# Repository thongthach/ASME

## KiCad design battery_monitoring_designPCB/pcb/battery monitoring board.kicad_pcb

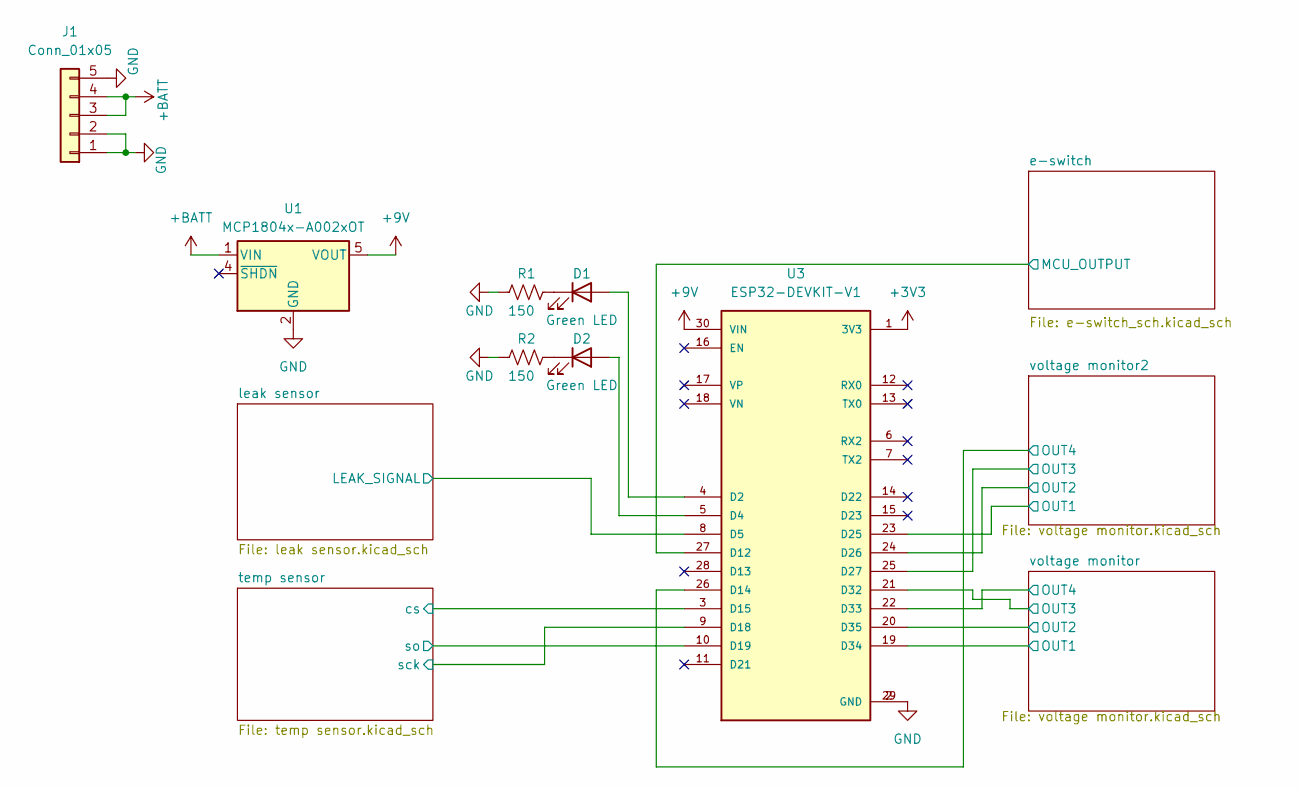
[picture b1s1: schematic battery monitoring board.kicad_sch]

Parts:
D1, D2: Green LED; D_0805_2012Metric_Pad1.15x1.40mm_HandSolder
J1: Conn_01x05; 1x5 Screw, 39970-0105 MOLEX
R1, R2: 150; R_0805_2012Metric_Pad1.20x1.40mm_HandSolder
U1: MCP1804x-A002xOT; SOT-23-5
U3: ESP32-DEVKIT-V1; MODULE_ESP32_DEVKIT_V1; PARTREV N/A

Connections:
+3V3: U3.1 (3V3); also elsewhere on the board
+9V: U1.5 (VOUT), U3.30 (VIN); also elsewhere on the board
+BATT: J1.3, J1.4, U1.1 (VIN); also elsewhere on the board
/e-switch/MCU_OUTPUT: U3.27 (D12); also elsewhere on the board
/leak sensor/LEAK_SIGNAL: U3.8 (D5); also elsewhere on the board
/temp sensor/cs: U3.3 (D15); also elsewhere on the board
/temp sensor/sck: U3.9 (D18); also elsewhere on the board
/temp sensor/so: U3.10 (D19); also elsewhere on the board
/voltage monitor2/OUT1: U3.23 (D25); also elsewhere on the board
/voltage monitor2/OUT2: U3.24 (D26); also elsewhere on the board
/voltage monitor2/OUT3: U3.25 (D27); also elsewhere on the board
/voltage monitor2/OUT4: U3.26 (D14); also elsewhere on the board
/voltage monitor/OUT1: U3.19 (D34); also elsewhere on the board
/voltage monitor/OUT2: U3.20 (D35); also elsewhere on the board
/voltage monitor/OUT3: U3.21 (D32); also elsewhere on the board
/voltage monitor/OUT4: U3.22 (D33); also elsewhere on the board
GND: J1.1, J1.2, J1.5, R1.1, R2.1, U1.2 (GND), U3.2 (GND), U3.29 (GND); also elsewhere on the board
unnamed: D1.2 (A), U3.4 (D2)
unnamed: D1.1 (K), R1.2
unnamed: D2.2 (A), U3.5 (D4)
unnamed: D2.1 (K), R2.2

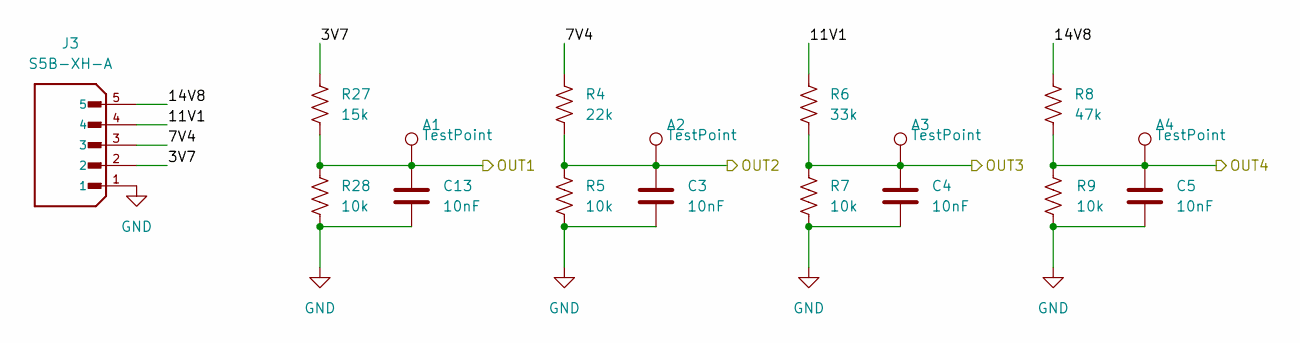
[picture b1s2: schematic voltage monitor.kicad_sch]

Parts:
A1, A2, A3, A4: TestPoint; TestPoint_Pad_1.0x1.0mm
C3, C4, C5, C13: 10nF; C_0805_2012Metric_Pad1.18x1.45mm_HandSolder
J3: S5B-XH-A; JST_S5B-XH-A; PARTREV 27-1-20
R4: 22k; R_0805_2012Metric_Pad1.20x1.40mm_HandSolder
R5, R7, R9, R28: 10k; R_0805_2012Metric_Pad1.20x1.40mm_HandSolder
R6: 33k; R_0805_2012Metric_Pad1.20x1.40mm_HandSolder
R8: 47k; R_0805_2012Metric_Pad1.20x1.40mm_HandSolder
R27: 15k; R_0805_2012Metric_Pad1.20x1.40mm_HandSolder

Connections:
/voltage monitor/3V7: J3.2, R27.2
/voltage monitor/7V4: J3.3, R4.2
/voltage monitor/11V1: J3.4, R6.2
/voltage monitor/14V8: J3.5, R8.2
/voltage monitor/OUT1: A1.1, C13.1, R27.1, R28.1; also elsewhere on the board
/voltage monitor/OUT2: A2.1, C3.1, R4.1, R5.1; also elsewhere on the board
/voltage monitor/OUT3: A3.1, C4.1, R6.1, R7.1; also elsewhere on the board
/voltage monitor/OUT4: A4.1, C5.1, R8.1, R9.2; also elsewhere on the board
GND: C3.2, C4.2, C5.2, C13.2, J3.1, R5.2, R7.2, R9.1, R28.2; also elsewhere on the board

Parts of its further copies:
B1, B2, B3, B4: TestPoint; TestPoint_Pad_1.0x1.0mm
C10, C11, C12, C14: 10nF; C_0805_2012Metric_Pad1.18x1.45mm_HandSolder
J9: S5B-XH-A; JST_S5B-XH-A; PARTREV 27-1-20
R20: 22k; R_0805_2012Metric_Pad1.20x1.40mm_HandSolder
R21, R23, R25, R30: 10k; R_0805_2012Metric_Pad1.20x1.40mm_HandSolder
R22: 33k; R_0805_2012Metric_Pad1.20x1.40mm_HandSolder
R24: 47k; R_0805_2012Metric_Pad1.20x1.40mm_HandSolder
R29: 15k; R_0805_2012Metric_Pad1.20x1.40mm_HandSolder

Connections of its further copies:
/voltage monitor2/3V7: J9.2, R29.2
/voltage monitor2/7V4: J9.3, R20.2
/voltage monitor2/11V1: J9.4, R22.2
/voltage monitor2/14V8: J9.5, R24.2
/voltage monitor2/OUT1: B1.1, C14.1, R29.1, R30.1; also elsewhere on the board
/voltage monitor2/OUT2: B2.1, C10.1, R20.1, R21.1; also elsewhere on the board
/voltage monitor2/OUT3: B3.1, C11.1, R22.1, R23.1; also elsewhere on the board
/voltage monitor2/OUT4: B4.1, C12.1, R24.1, R25.2; also elsewhere on the board
GND: C10.2, C11.2, C12.2, C14.2, J9.1, R21.2, R23.2, R25.1, R30.2; also elsewhere on the board

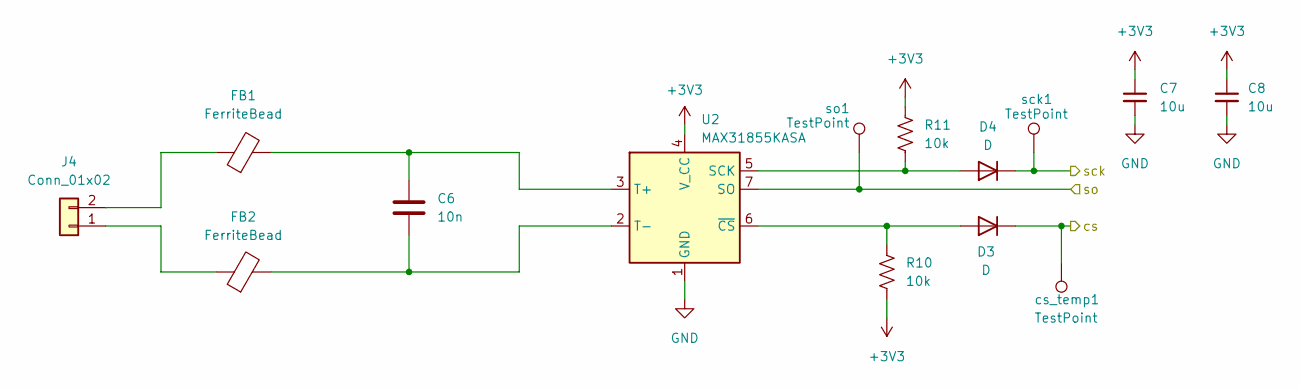
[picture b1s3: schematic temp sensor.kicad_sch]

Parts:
C6: 10n; C_0805_2012Metric_Pad1.18x1.45mm_HandSolder
C7, C8: 10u; C_0805_2012Metric_Pad1.18x1.45mm_HandSolder
D3, D4: D; D_0805_2012Metric_Pad1.15x1.40mm_HandSolder
FB1, FB2: FerriteBead; C_0805_2012Metric
J4: Conn_01x02; TE_282836-2; Part Number 1-0201FBV0T
R10, R11: 10k; R_0805_2012Metric_Pad1.20x1.40mm_HandSolder
U2: MAX31855KASA; SOIC-8_3.9x4.9mm_P1.27mm
cs_temp1: TestPoint; TestPoint_Pad_1.0x1.0mm
sck1: TestPoint; TestPoint_Pad_1.0x1.0mm
so1: TestPoint; TestPoint_Pad_1.0x1.0mm

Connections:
+3V3: C7.1, C8.1, R10.2, R11.1, U2.4 (V_CC); also elsewhere on the board
/temp sensor/cs: D3.1 (K), cs_temp1.1; also elsewhere on the board
/temp sensor/sck: D4.1 (K), sck1.1; also elsewhere on the board
/temp sensor/so: U2.7 (SO), so1.1; also elsewhere on the board
GND: C7.2, C8.2, U2.1 (GND); also elsewhere on the board
unnamed: D3.2 (A), R10.1, U2.6 (~CS)
unnamed: D4.2 (A), R11.2, U2.5 (SCK)
unnamed: FB2.1, J4.1
unnamed: FB1.1, J4.2
unnamed: C6.1, FB1.2, U2.3 (T+)
unnamed: C6.2, FB2.2, U2.2 (T-)

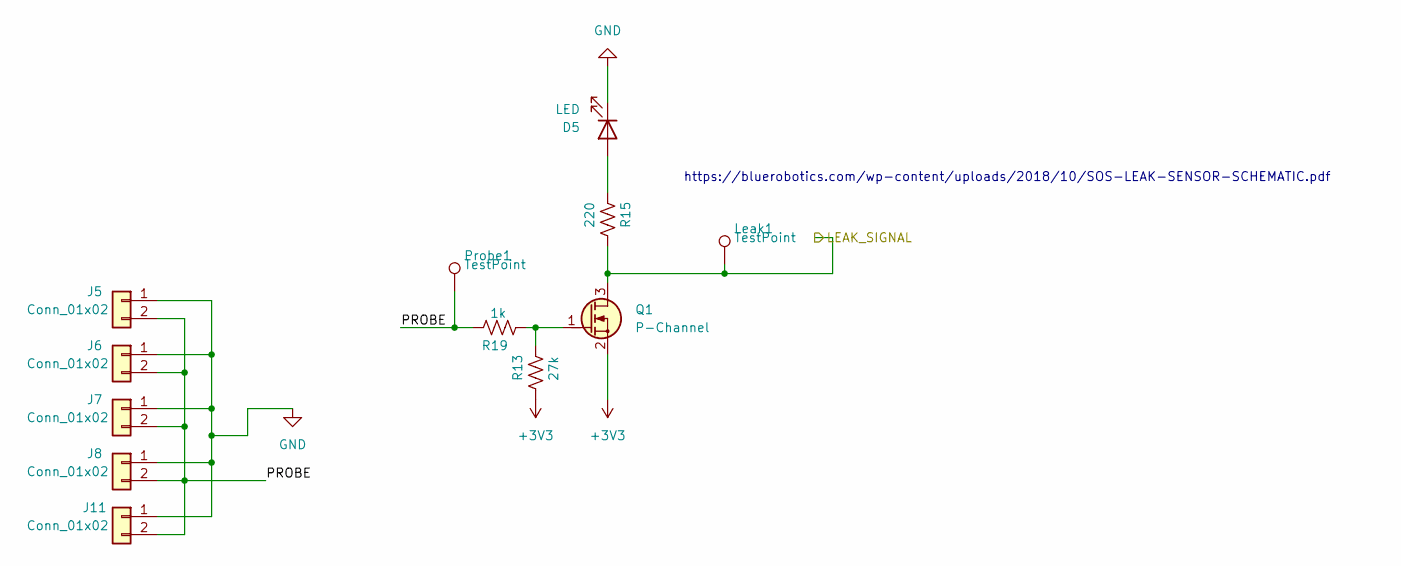
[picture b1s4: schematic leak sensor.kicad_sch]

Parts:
D5: LED; D_0805_2012Metric_Pad1.15x1.40mm_HandSolder
J5, J6, J7, J8, J11: Conn_01x02; PinHeader_1x02_P1.27mm_Vertical
Leak1: TestPoint; TestPoint_Pad_1.0x1.0mm
Probe1: TestPoint; TestPoint_Pad_1.0x1.0mm
Q1: P-Channel; SOT-23
R13: 27k; R_0805_2012Metric_Pad1.20x1.40mm_HandSolder
R15: 220; R_0805_2012Metric_Pad1.20x1.40mm_HandSolder
R19: 1k; R_0805_2012Metric_Pad1.20x1.40mm_HandSolder

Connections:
+3V3: Q1.2 (S), R13.2; also elsewhere on the board
/leak sensor/LEAK_SIGNAL: Leak1.1, Q1.3 (D), R15.2; also elsewhere on the board
/leak sensor/PROBE: J5.2, J6.2, J7.2, J8.2, J11.2, Probe1.1, R19.1
GND: D5.1 (K), J5.1, J6.1, J7.1, J8.1, J11.1; also elsewhere on the board
unnamed: D5.2 (A), R15.1
unnamed: Q1.1 (G), R13.1, R19.2

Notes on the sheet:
https://bluerobotics.com/wp-content/uploads/2018/10/SOS-LEAK-SENSOR-SCHEMATIC.pdf

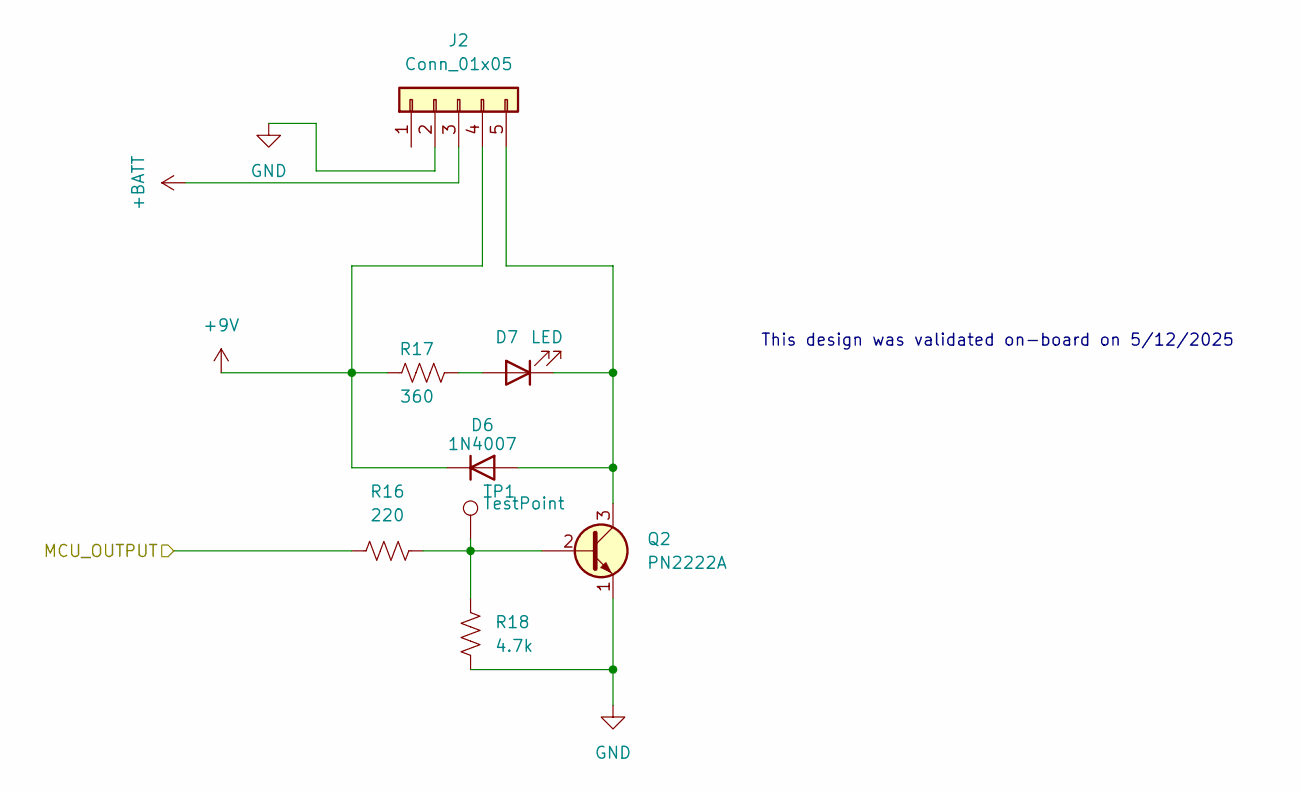
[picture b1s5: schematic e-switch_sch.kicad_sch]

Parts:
D6: 1N4007; D_SMA
D7: LED; D_0805_2012Metric_Pad1.15x1.40mm_HandSolder
J2: Conn_01x05; 1x5 Screw, 39970-0105 MOLEX
Q2: PN2222A; TO-92
R16: 220; R_0805_2012Metric_Pad1.20x1.40mm_HandSolder
R17: 360; R_0805_2012Metric_Pad1.20x1.40mm_HandSolder
R18: 4.7k; R_0805_2012Metric_Pad1.20x1.40mm_HandSolder
TP1: TestPoint; TestPoint_Pad_1.0x1.0mm

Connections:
+9V: D6.1 (K), J2.4, R17.1; also elsewhere on the board
+BATT: J2.3; also elsewhere on the board
/e-switch/MCU_OUTPUT: R16.1; also elsewhere on the board
GND: J2.2, J2.2A, Q2.1 (E), R18.2; also elsewhere on the board
unnamed: D6.2 (A), D7.1 (K), J2.5, Q2.3 (C)
unnamed: D7.2 (A), R17.2
unnamed: Q2.2 (B), R16.2, R18.1, TP1.1

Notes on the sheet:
This design was validated on-board on 5/12/2025

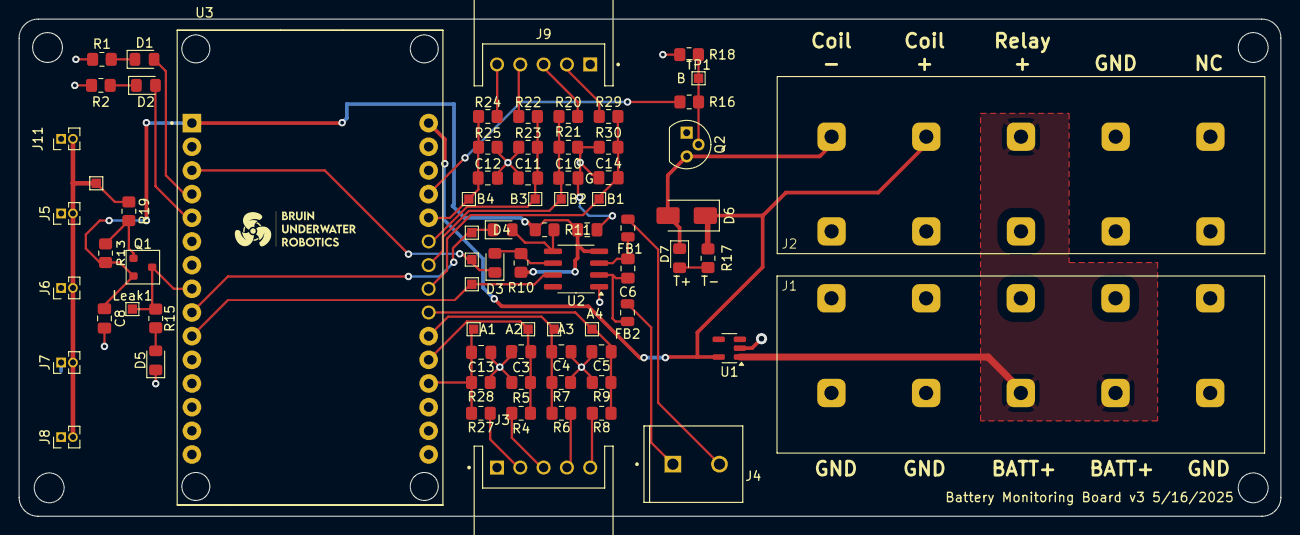
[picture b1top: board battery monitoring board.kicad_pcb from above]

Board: 2 copper layers, 135.4 x 53.3 mm, 75 parts (0 on the bottom side), 41 nets.

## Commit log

2025-06-19 Create temp
